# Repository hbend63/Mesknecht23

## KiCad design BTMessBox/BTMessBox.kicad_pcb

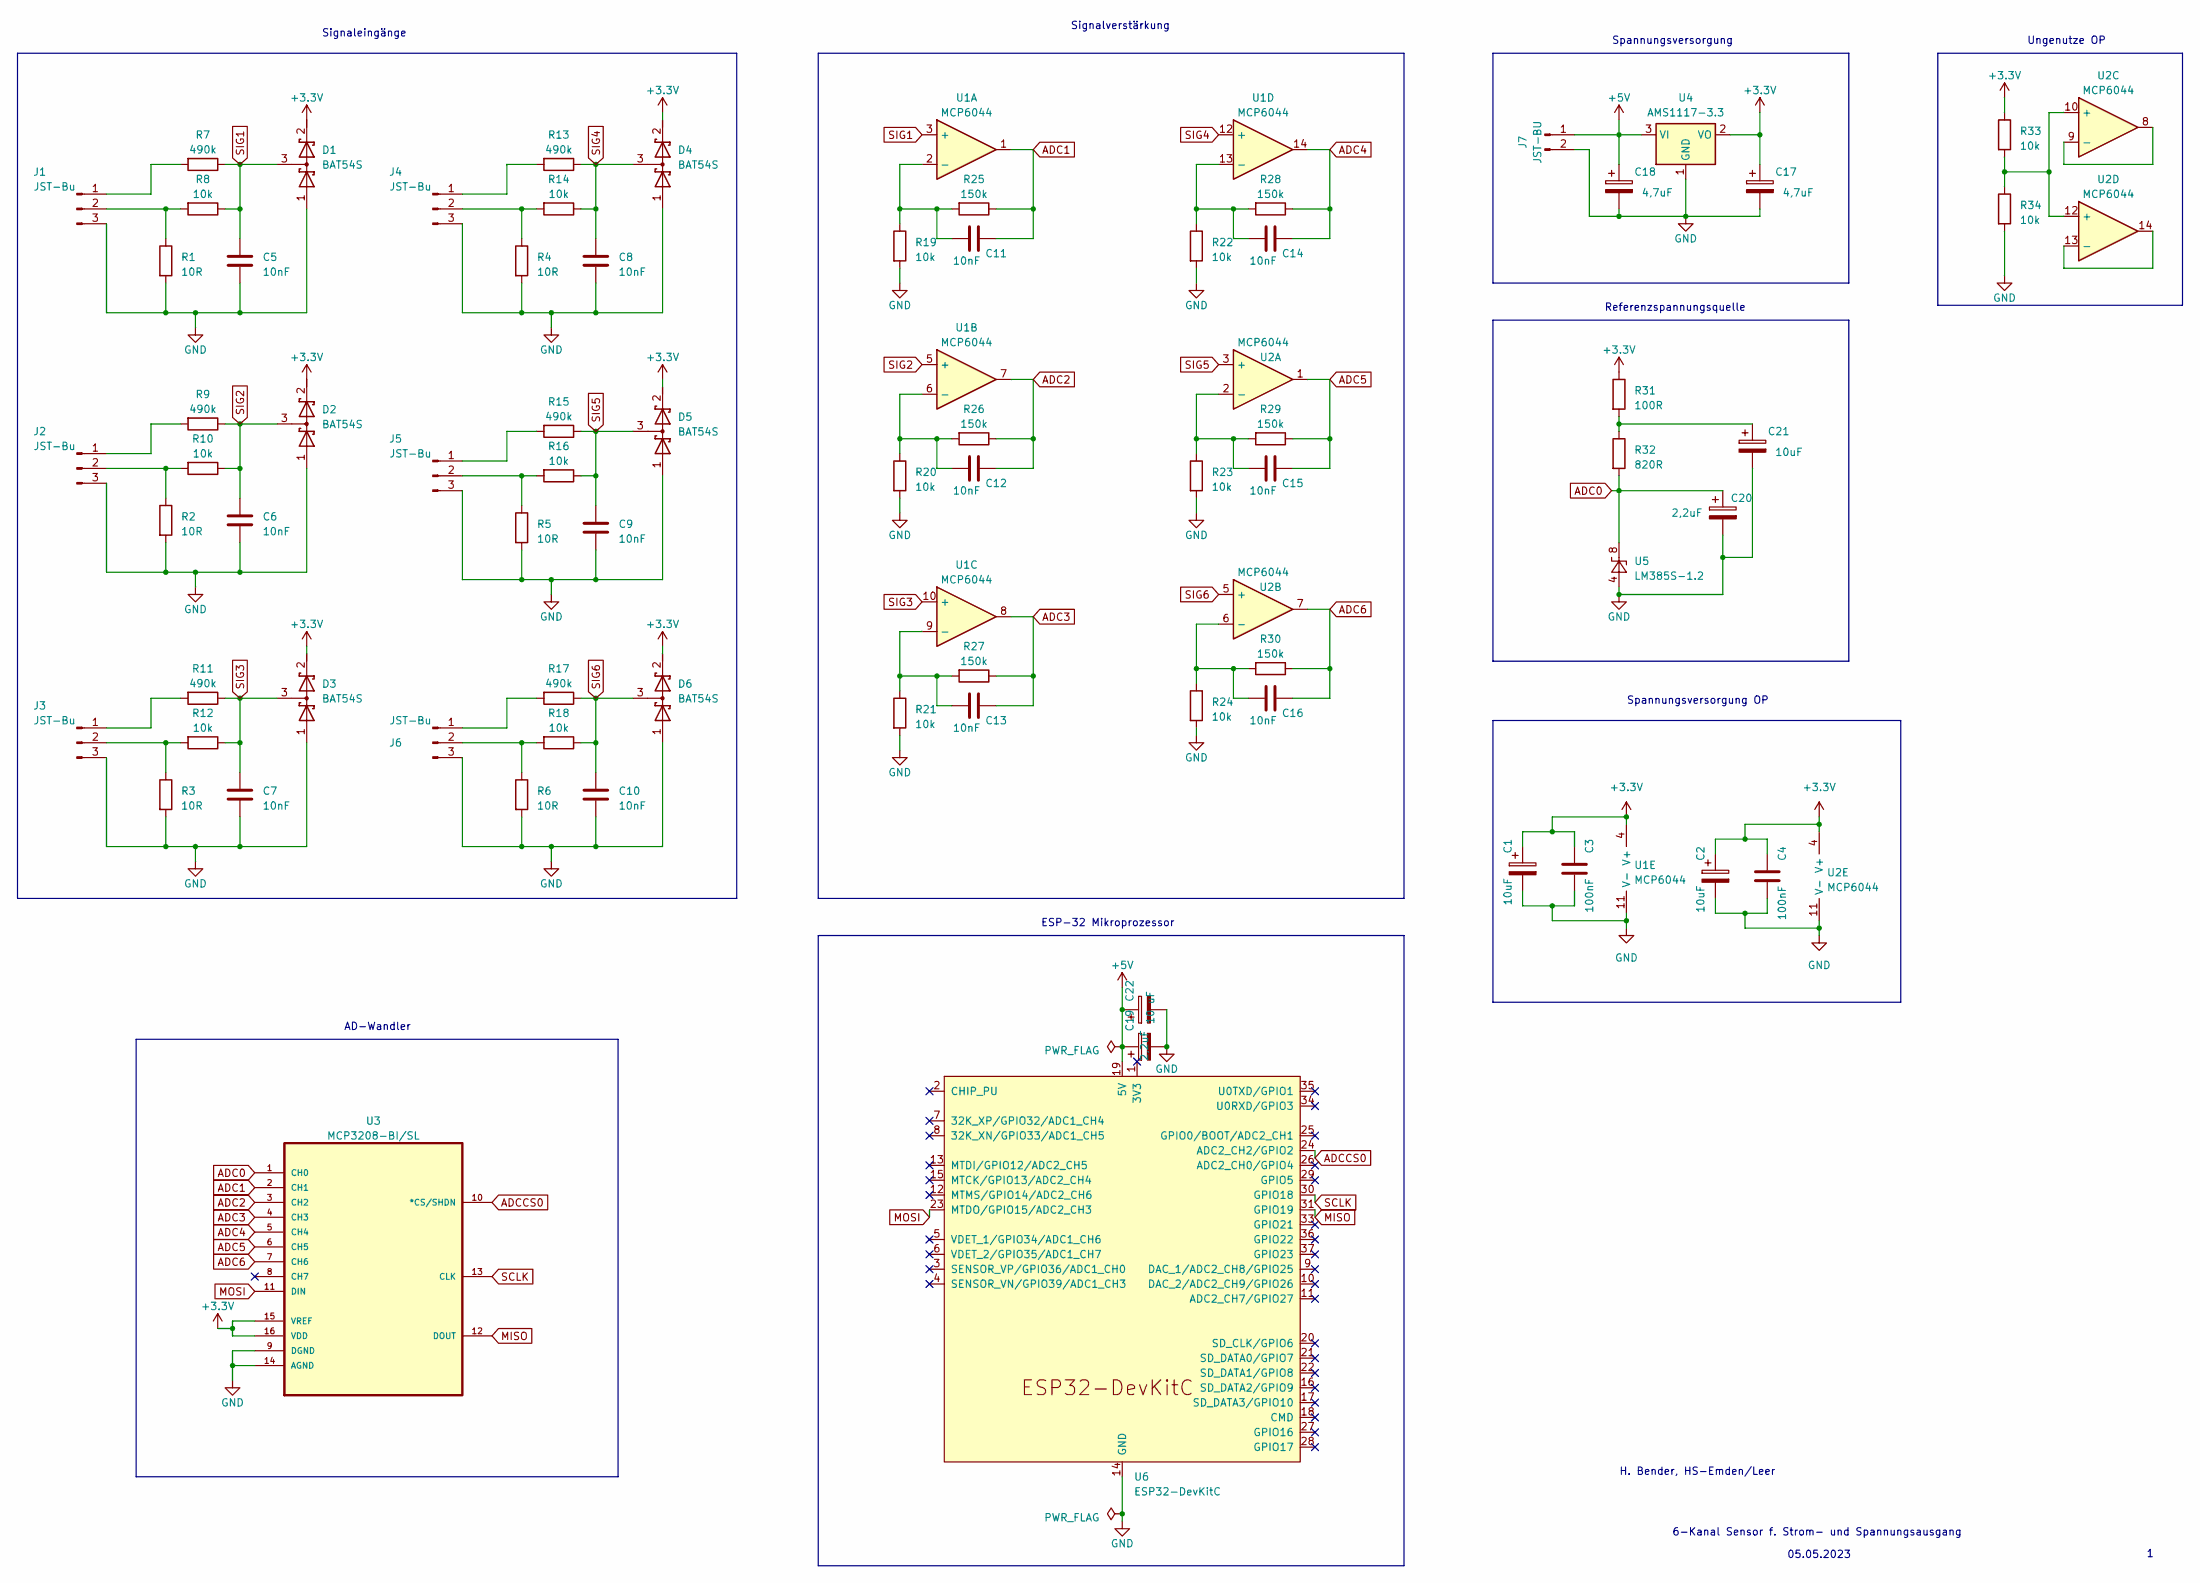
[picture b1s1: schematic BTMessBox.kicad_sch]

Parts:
C1, C2, C21: 10uF; CP_Elec_5x3
C3, C4: 100nF; C_0805_2012Metric_Pad1.18x1.45mm_HandSolder
C5, C6, C7, C8, C9, C10, C11, C12, C13, C14, C15, C16: 10nF; C_0805_2012Metric_Pad1.18x1.45mm_HandSolder
C17, C18: 4,7uF; C_1210_3225Metric
C19: 10 uF; CP_Elec_5x3
C20, C22: 2,2uF; C_1210_3225Metric
D1, D2, D3, D4, D5, D6: BAT54S; TSOT-23
J1, J2, J3, J4, J5, J6: JST-Bu; JST_EH_B3B-EH-A_1x03_P2.50mm_Vertical
J7: JST-BU; JST_EH_B2B-EH-A_1x02_P2.50mm_Vertical
R1, R2, R3, R4, R5, R6: 10R; R_0805_2012Metric_Pad1.20x1.40mm_HandSolder
R7, R9, R11, R13, R15, R17: 490k; R_0805_2012Metric_Pad1.20x1.40mm_HandSolder
R8, R10, R12, R14, R16, R18, R19, R20, R21, R22, R23, R24, R33, R34: 10k; R_0805_2012Metric_Pad1.20x1.40mm_HandSolder
R25, R26, R27, R28, R29, R30: 150k; R_0805_2012Metric_Pad1.20x1.40mm_HandSolder
R31: 100R; R_0805_2012Metric_Pad1.20x1.40mm_HandSolder
R32: 820R; R_0805_2012Metric_Pad1.20x1.40mm_HandSolder
U1, U2: MCP6044; SOIC-14_3.9x8.7mm_P1.27mm
U3: MCP3208-BI/SL; SOIC127P600X175-16N; MPN MCP3208-BI/SL
U4: AMS1117-3.3; SOT-223-3_TabPin2
U5: LM385S-1.2; SOIC-8_3.9x4.9mm_P1.27mm
U6: ESP32-DevKitC

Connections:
+3.3V: C1.1, C2.1, C3.1, C4.1, C17.1, D1.2 (K), D2.2 (K), D3.2 (K), D4.2 (K), D5.2 (K), D6.2 (K), R31.1, R33.1, U1.4 (V+), U2.4 (V+), U3.15 (VREF), U3.16 (VDD), U4.2 (VO)
+5V: C18.1, C19.1, C22.1, J7.1, U4.3 (VI), U6.19 (5V)
ADC0: C20.1, R32.2, U3.1 (CH0), U5.6 (K), U5.8 (K)
ADC1: C11.2, R25.1, U1.1, U3.2 (CH1)
ADC2: C12.2, R26.1, U1.7, U3.3 (CH2)
ADC3: C13.2, R27.1, U1.8, U3.4 (CH3)
ADC4: C14.2, R28.1, U1.14, U3.5 (CH4)
ADC5: C15.2, R29.1, U2.1, U3.6 (CH5)
ADC6: C16.2, R30.1, U2.7, U3.7 (CH6)
ADCCS0: U3.10 (*CS/SHDN), U6.24 (ADC2_CH2/GPIO2)
GND: C1.2, C2.2, C3.2, C4.2, C5.2, C6.2, C7.2, C8.2, C9.2, C10.2, C17.2, C18.2, C19.2, C20.2, C21.2, C22.2, D1.1 (A), D2.1 (A), D3.1 (A), D4.1 (A), D5.1 (A), D6.1 (A), J1.3, J2.3, J3.3, J4.3, J5.3, J6.3, J7.2, R1.2, R2.2, R3.2, R4.2, R5.2, R6.2, R19.2, R20.2, R21.2, R22.2, R23.2, R24.2, R34.2, U1.11 (V-), U2.11 (V-), U3.9 (DGND), U3.14 (AGND), U4.1 (GND), U5.4 (A), U6.14 (GND), U6.32 (GND), U6.38 (GND)
MISO: U3.12 (DOUT), U6.31 (GPIO19)
MOSI: U3.11 (DIN), U6.23 (MTDO/GPIO15/ADC2_CH3)
unnamed: C21.1, R31.2, R32.1
unnamed: J1.1, R7.2
unnamed: J1.2, R1.1, R8.2
unnamed: J2.1, R9.2
unnamed: J2.2, R2.1, R10.2
unnamed: J3.1, R11.2
unnamed: J3.2, R3.1, R12.2
unnamed: J4.1, R13.2
unnamed: J4.2, R4.1, R14.2
unnamed: J5.1, R15.2
unnamed: J5.2, R5.1, R16.2
unnamed: J6.1, R17.2
unnamed: J6.2, R6.1, R18.2
unnamed: C11.1, R19.1, R25.2, U1.2 (-)
unnamed: C12.1, R20.1, R26.2, U1.6 (-)
unnamed: C13.1, R21.1, R27.2, U1.9 (-)
unnamed: C14.1, R22.1, R28.2, U1.13 (-)
unnamed: C15.1, R23.1, R29.2, U2.2 (-)
unnamed: C16.1, R24.1, R30.2, U2.6 (-)
unnamed: R33.2, R34.1, U2.10 (+), U2.12 (+)
unnamed: U2.8, U2.9 (-)
unnamed: U2.13 (-), U2.14
SCLK: U3.13 (CLK), U6.30 (GPIO18)
SIG1: C5.1, D1.3 (common), R7.1, R8.1, U1.3 (+)
SIG2: C6.1, D2.3 (common), R9.1, R10.1, U1.5 (+)
SIG3: C7.1, D3.3 (common), R11.1, R12.1, U1.10 (+)
SIG4: C8.1, D4.3 (common), R13.1, R14.1, U1.12 (+)
SIG5: C9.1, D5.3 (common), R15.1, R16.1, U2.3 (+)
SIG6: C10.1, D6.3 (common), R17.1, R18.1, U2.5 (+)

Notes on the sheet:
6-Kanal Sensor f. Strom- und Spannungsausgang
H. Bender, HS-Emden/Leer
Spannungsversorgung OP
Signaleingänge
ESP-32 Mikroprozessor
Referenzspannungsquelle
Ungenutze OP
05.05.2023
Signalverstärkung
Spannungsversorgung
AD-Wandler

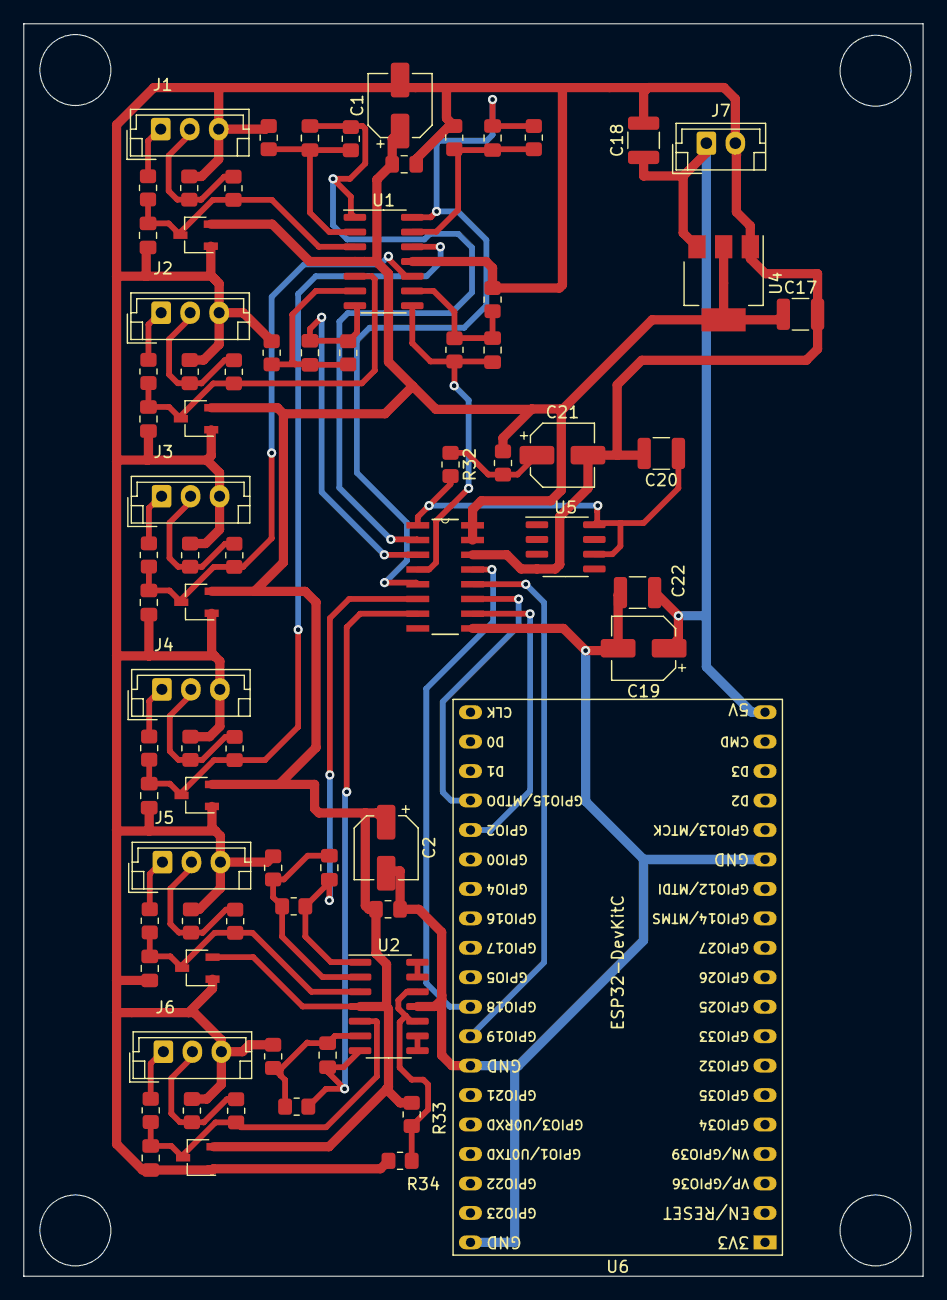
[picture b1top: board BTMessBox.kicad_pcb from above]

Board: 2 copper layers, 77.5 x 108.0 mm, 75 parts (0 on the bottom side), 42 nets.

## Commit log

2023-08-10 Layout PCB
2023-09-06 MessknechtSW
2023-09-06 test
2023-09-07 adc korrekturwert eingefügt
2023-09-08 Liveansicht korrigiert
2023-09-11 Sensorname hinzugefügt
2023-09-13 Anpassungen
2023-09-18 Messung ADC korrigiert
2024-05-29 mcp-read ersetzt u. cad-dateien für gehäuse
